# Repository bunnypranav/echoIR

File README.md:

# EchoIR

This is an IR hub, with both an IR receiver and a handful of transmitters, which can control my IR appliances, like the AC, fan, and TV, with my phone and over the internet. It wouldn't replace the remotes, but it could learn their signals and replay them whenever I want from my phone.

# Schematic
*Made in KiCad*

On the left side is the USB-C connector, going into the polyfuse, then into the +5V rail. The three IR LEDs each have their own 33-ohm resistor and connect from +5V to the IRLEDNODE. When the MOSFET turns on, current flows through all three LEDs to ground. The TSOP38238 receiver runs from +3.3V, which comes from the Pico's internal regulator. There is a 100nF capacitor and a 4.7uF capacitor close to it, because IR receivers are sensitive to noise. The button connected to GPIO 14 controls the "record" mode, with its status led just being the inbuilt Pi led at GPIO25.

# PCB
*Made in KiCad*

# Firmware
*Written in CircuitPython*

The Pico 2W connects to WiFi on boot and starts a HTTP server that exposes a simple webhook endpoint. When I press the button, it enters a short recording window and captures the raw pulse timings from the TSOP38238, then stores them in memory with an incrementing ID number. The IR LEDs are driven from GPIO5 using a 38kHz PWM carrier, and when a POST request is sent to `/play` with a JSON body like `{"id": 3}`, the Pico looks up that stored signal and replays it through the three IR transmitters. Everything runs locally on the Pico, so another computer on the same network can trigger appliances just by sending a simple HTTP request. This can also be easily plugged in to home automation services, or be modified to worth with MQTT, something I plan to do in the future.

# CAD Base
*Designed in Fusion 360*

Created a basic CAD base for the PCB to sit on. I did not create any top cover, since the LEDs cannot shine through solid PLA plastic, neither can the TSOP recieve IR pulses. This is just to prevent the bottom pins from scratching the surface I put this on.

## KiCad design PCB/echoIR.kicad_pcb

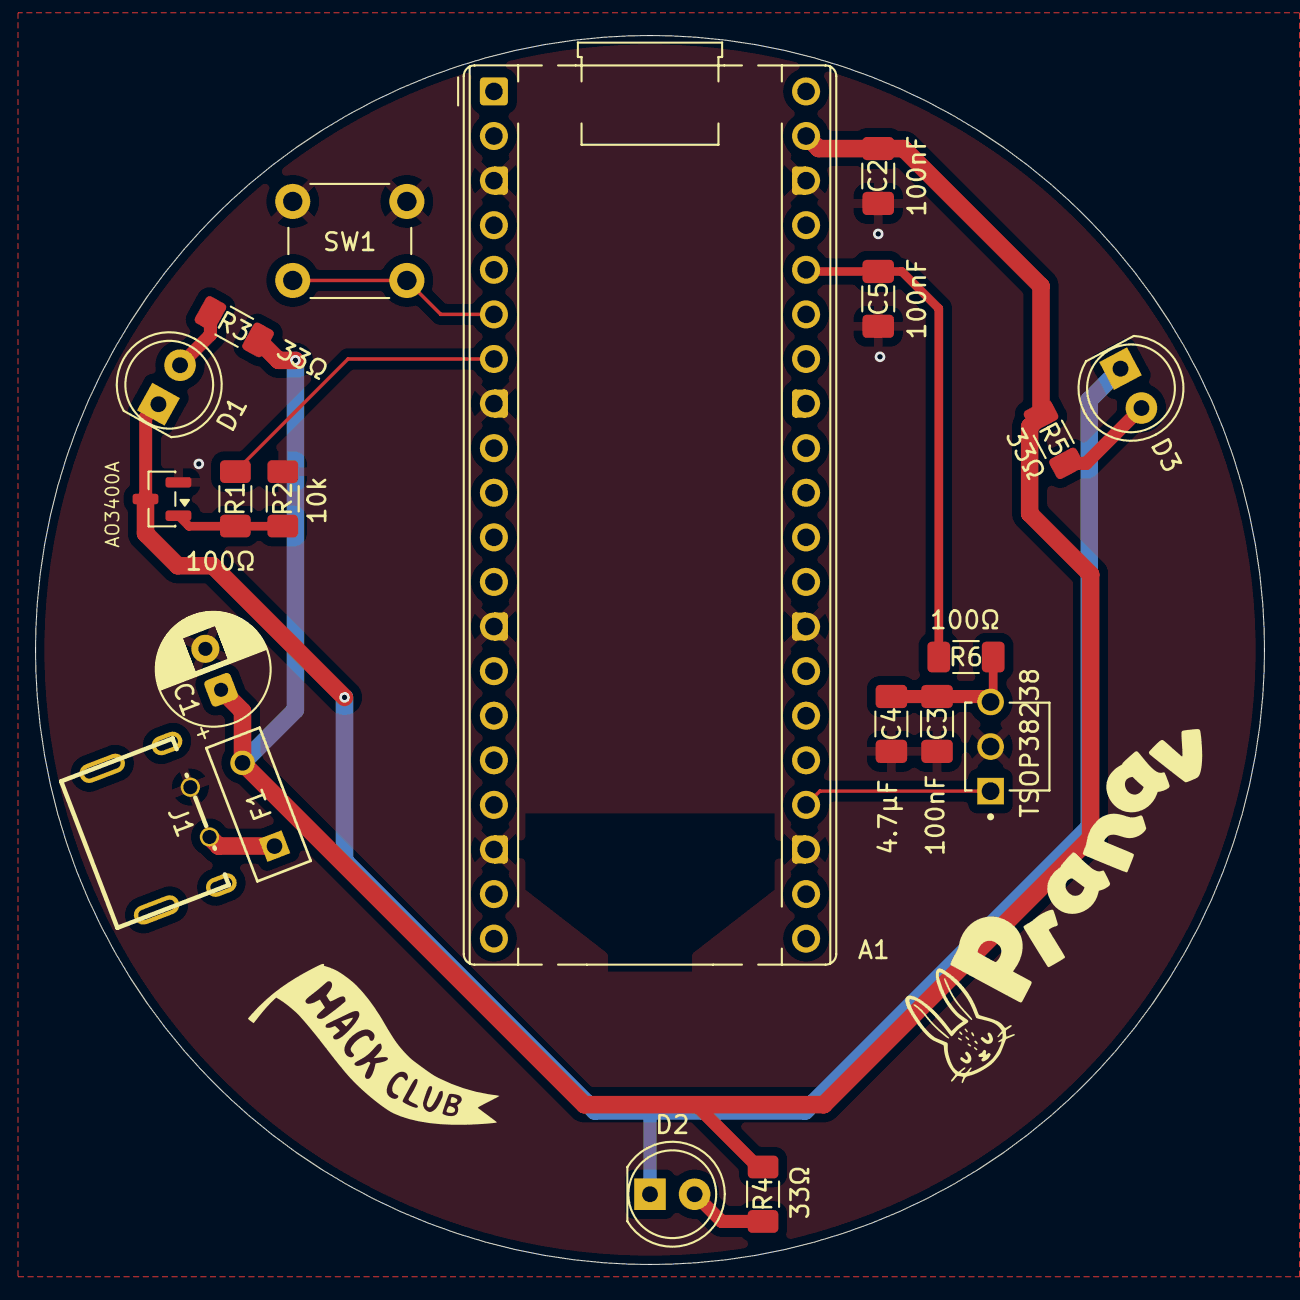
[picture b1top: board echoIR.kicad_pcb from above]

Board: 2 copper layers, 70.0 x 70.0 mm, 20 parts (0 on the bottom side), 13 nets.

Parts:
A1: RaspberryPi_Pico_W; RaspberryPi_Pico_Common_THT
A2: TSOP38238; XDCR_TSOP38238
C1: 10µF; CP_Radial_D6.3mm_P2.50mm
C2, C3, C5: 100nF; C_1206_3216Metric_Pad1.33x1.80mm_HandSolder
C4: 4.7µF; C_1206_3216Metric_Pad1.33x1.80mm_HandSolder
D1, D2, D3: LED; LED_D5.0mm
F1: Polyfuse; FUS_RXEF050_TYCO_TYC
J1: USB_C_Receptacle_PowerOnly_6P; USB-C-TH_TYPE-C-31-M-33
Q1: AO3400A; SOT-23
R1, R6: 100Ω; R_1206_3216Metric_Pad1.30x1.75mm_HandSolder
R2: 10k; R_1206_3216Metric_Pad1.30x1.75mm_HandSolder
R3, R4, R5: 33Ω; R_1206_3216Metric_Pad1.30x1.75mm_HandSolder
SW1: SW_Push; SW_PUSH_6mm

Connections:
+3.3V: A1.36 (3V3), C5.1, R6.2
+5V: A1.39 (VSYS), C1.1, C2.2, F1.2, R3.1, R4.1, R5.1
GND: A1.3 (GND), A1.8 (GND), A1.13 (GND), A1.18 (GND), A1.23 (GND), A1.28 (GND), A1.38 (GND), A2.2 (GND), C1.2, C2.1, C3.2, C4.2, C5.2, J1.B12 (GND), Q1.2 (S), R2.2, SW1.1
GP16: A1.24 (GPIO18), A2.1 (OUT)
IRLEDNODE: D1.1 (K), D2.1 (K), D3.1 (K), Q1.3 (D)
IRTX: A1.7 (GPIO5), R1.1
unnamed: A1.6 (GPIO4), SW1.2
unnamed: A2.3 (VS), C3.1, C4.1, R6.1
unnamed: D1.2 (A), R3.2
unnamed: D2.2 (A), R4.2
unnamed: D3.2 (A), R5.2
unnamed: F1.1, J1.A9 (VBUS)
unnamed: Q1.1 (G), R1.2, R2.1

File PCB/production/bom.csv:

Designator,Footprint,Quantity,Value,LCSC Part #
A1,RaspberryPi_Pico_Common_THT,1,RaspberryPi_Pico_W,
A2,XDCR_TSOP38238,1,TSOP38238,
C1,CP_Radial_D6.3mm_P2.50mm,1,10µF,
"C2, C3, C5",1206,3,100nF,
C4,1206,1,4.7µF,
"D1, D2, D3",LED_D5.0mm,3,LED,
F1,FUS_RXEF050_TYCO_TYC,1,Polyfuse,
J1,USB-C-TH_TYPE-C-31-M-33,1,USB_C_Receptacle_PowerOnly_6P,
Q1,SOT-23,1,AO3400A,
"R1, R6",1206,2,100Ω,
R2,1206,1,10k,
"R3, R4, R5",1206,3,33Ω,
SW1,SW_PUSH_6mm,1,SW_Push,

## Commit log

2026-02-28 Add firmware
2026-03-01 update journal
